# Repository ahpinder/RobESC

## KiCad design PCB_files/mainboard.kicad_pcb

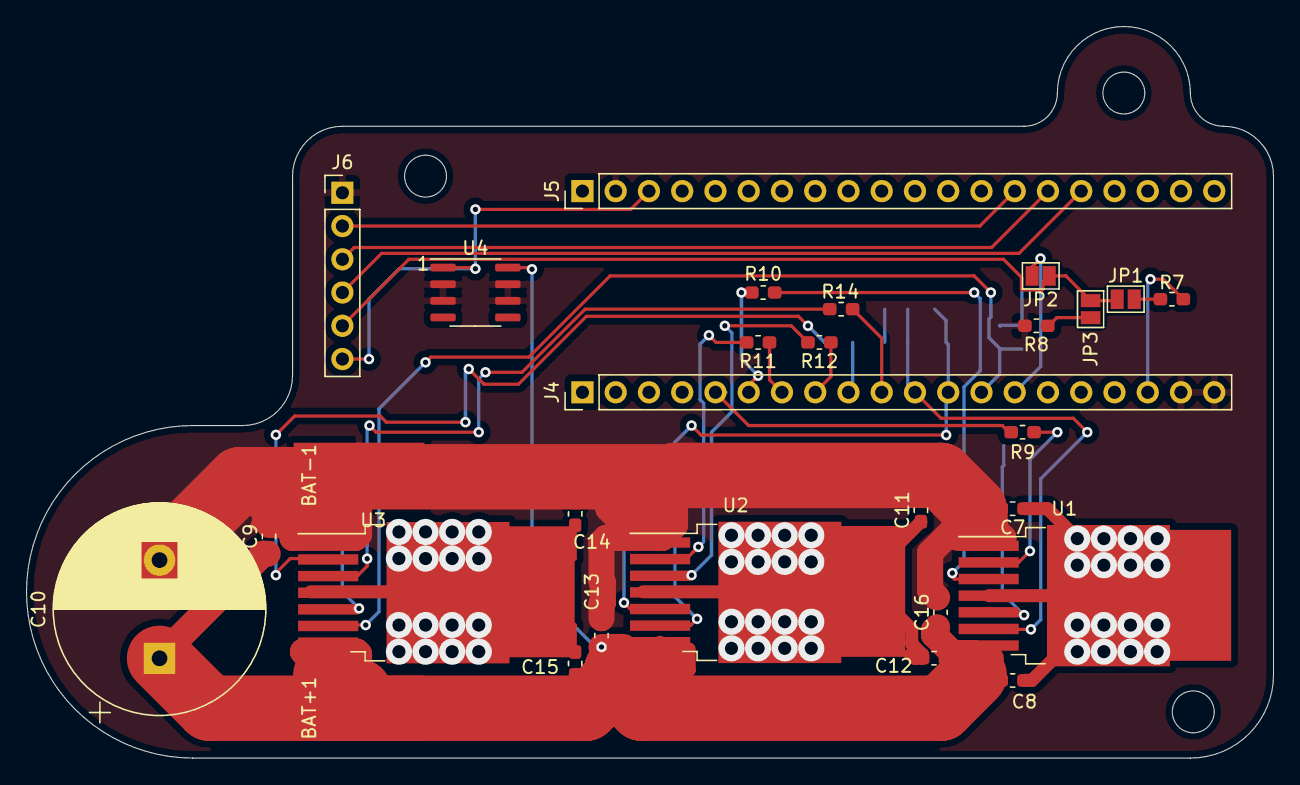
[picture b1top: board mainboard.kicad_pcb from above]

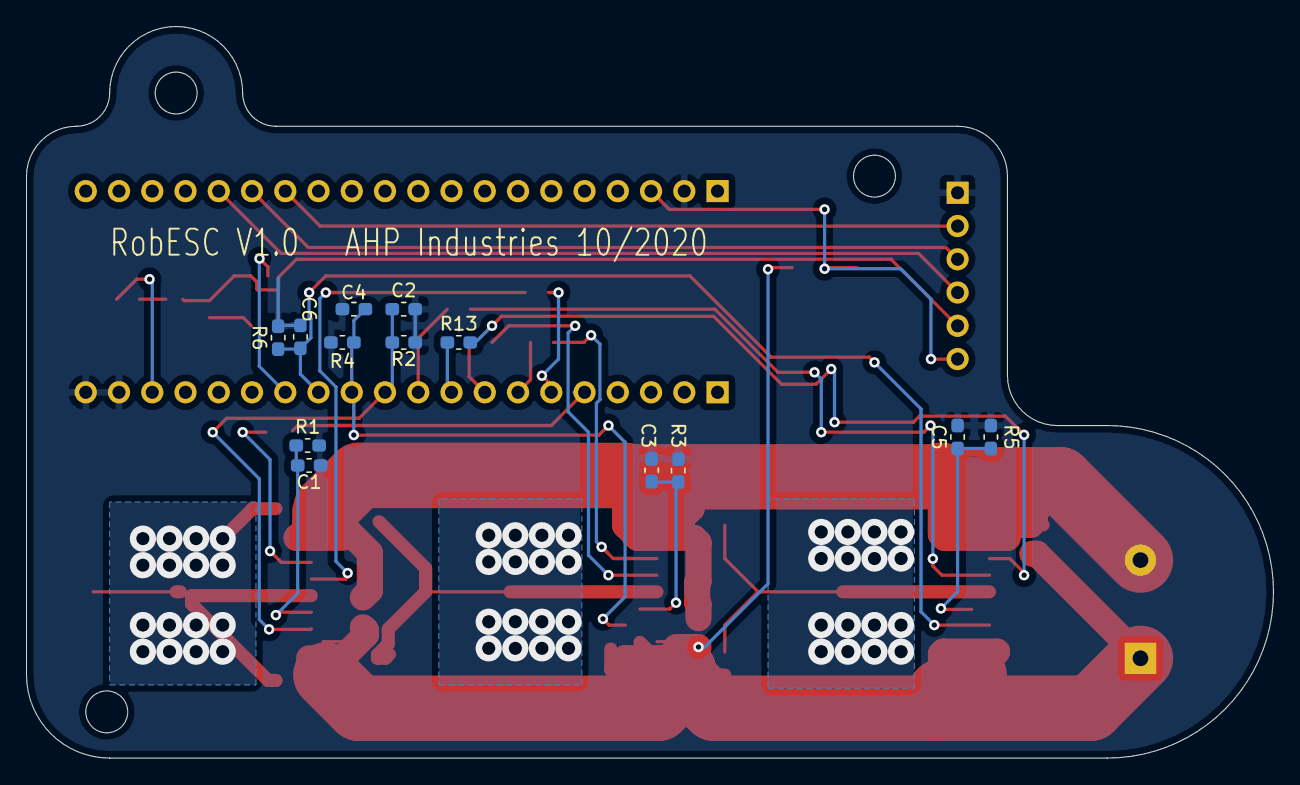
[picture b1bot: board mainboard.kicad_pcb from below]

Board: 2 copper layers, 95.2 x 55.9 mm, 45 parts (13 on the bottom side), 32 nets.

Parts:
BAT+1: Conn_01x01_Male; SolderWirePad_1x01_SMD_5x10mm
BAT-1: Conn_01x01_Male; SolderWirePad_1x01_SMD_5x10mm
C1, C3, C5, C9, C13, C16: 100n; C_0603_1608Metric_Pad1.05x0.95mm_HandSolder
C2, C4, C6: 1n; C_0603_1608Metric_Pad1.05x0.95mm_HandSolder
C7, C8, C11, C12, C14, C15: 220n; C_0603_1608Metric_Pad1.05x0.95mm_HandSolder
C10: 1000u; CP_Radial_D16.0mm_P7.50mm
J1, J2, J3: Conn_01x01_Male; SolderWirePad_1x01_SMD_5x10mm
J4, J5: Conn_01x20; PinHeader_1x20_P2.54mm_Vertical
J6: Conn_01x06_Male; PinHeader_1x06_P2.54mm_Vertical
JP1, JP2, JP3: SolderJumper_2_Open; SolderJumper-2_P1.3mm_Open_Pad1.0x1.5mm
R1, R3, R5: 0.51K; R_0603_1608Metric_Pad1.05x0.95mm_HandSolder
R2, R4, R6: 1K; R_0603_1608Metric_Pad1.05x0.95mm_HandSolder
R7, R8: R; R_0603_1608Metric_Pad1.05x0.95mm_HandSolder
R9, R10, R11, R12, R13, R14: 10K; R_0603_1608Metric_Pad1.05x0.95mm_HandSolder
U1, U2, U3: IFX007TAUMA1; TO-263-7_TabPin8
U4: LM2931-5.0_SO8; SOIC-8_3.9x4.9mm_P1.27mm

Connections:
+3V3: J4.18, R7.1
+BATT: BAT+1.1, C8.1, C9.1, C10.1, C12.1, C13.1, C15.1, C16.1, U1.7, U2.7, U3.7, U4.8
/sr1: C1.1, R1.1, U1.5
/sr2: C3.1, R3.1, U2.5
/sr3: C5.1, R5.1, U3.5
GND: BAT-1.1, C1.2, C2.2, C3.2, C4.2, C5.2, C6.2, C7.2, C9.2, C10.2, C11.2, C13.2, C14.2, C16.2, J4.19, J4.20, J5.2, J6.1, R1.2, R2.2, R3.2, R4.2, R5.2, R6.2, R8.2, U1.1, U2.1, U3.1, U4.2, U4.3, U4.6, U4.7
unnamed: C2.1, J4.11, R2.1, U1.6
unnamed: C4.1, J4.12, R4.1, U2.6
unnamed: C6.1, J4.13, R6.1, U3.6
unnamed: C7.1, C8.2, J1.1, U1.4, U1.8
unnamed: C11.1, C12.2, J2.1, U2.4, U2.8
unnamed: C14.1, C15.2, J3.1, U3.4, U3.8
unnamed: J4.5, R9.1
unnamed: J4.6, R10.1
unnamed: J4.7, R11.1
unnamed: J4.8, R12.1
unnamed: J4.9, R13.1
unnamed: J4.10, R14.1
unnamed: J4.14, JP2.2
unnamed: J5.14, J6.2
unnamed: J5.15, J6.3
unnamed: J5.16, J6.4
unnamed: J6.5, JP1.1, JP2.1, JP3.1
unnamed: JP1.2, R7.2
unnamed: JP3.2, R8.1
unnamed: R9.2, U1.2
unnamed: R10.2, U1.3
unnamed: R11.2, U2.2
unnamed: R12.2, U2.3
unnamed: R13.2, U3.2
unnamed: R14.2, U3.3
VCC: J5.3, J6.6, U4.1

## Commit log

2020-09-27 Added KiCad design files
2020-09-29 Added protection and voltage regulation circuitry
2020-09-29 Started routing components
2020-09-29 Finished routing and added footprint file for driver chip
2020-10-01 fixed half-bridge driver footprints
2020-10-04 Optimized ground planes and added thermal vias to half-bridges
2020-10-05 Optimized routing and schematic clarity
2020-10-06 Minor PCB fixes + added gerber and drill files (in zip)
